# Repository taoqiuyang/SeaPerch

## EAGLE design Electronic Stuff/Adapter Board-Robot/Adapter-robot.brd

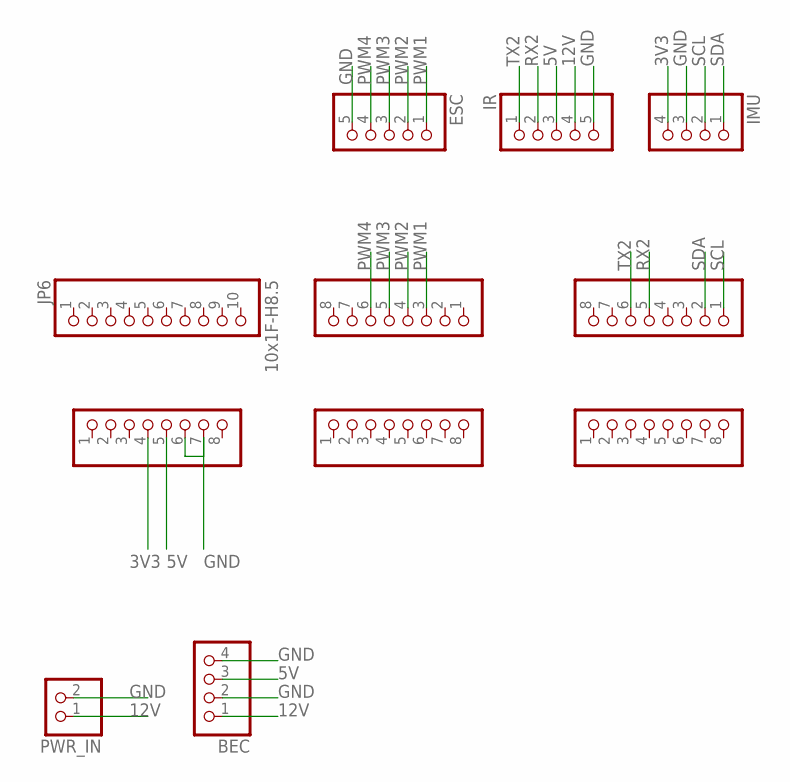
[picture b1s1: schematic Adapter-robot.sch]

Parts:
ADCH: 8x1F-H8.5; 1X08
ADCL: 8x1F-H8.5; 1X08
BEC: PINHD-1X4; 1X04
COMMUNICATION: 8x1F-H8.5; 1X08
ESC: PINHD-1X5; 1X05
IMU: PINHD-1X4; 1X04
IR: PINHD-1X5; 1X05
JP6: 10x1F-H8.5; 1X10
POWER: 8x1F-H8.5; 1X08
PWML: 8x1F-H8.5; 1X08
PWR_IN: PINHD-1X2; 1X02

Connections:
3V3: IMU.4, POWER.4
5V: BEC.3, IR.3, POWER.5
12V: BEC.1, IR.4, PWR_IN.1
GND: BEC.2, BEC.4, ESC.5, IMU.3, IR.5, POWER.6, POWER.7, PWR_IN.2
PWM1: ESC.1, PWML.3
PWM2: ESC.2, PWML.4
PWM3: ESC.3, PWML.5
PWM4: ESC.4, PWML.6
RX2: COMMUNICATION.5, IR.2
SCL: COMMUNICATION.1, IMU.2
SDA: COMMUNICATION.2, IMU.1
TX2: COMMUNICATION.6, IR.1

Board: 2 copper layers, 11 parts (0 on the bottom side), 12 nets, no tracks yet.

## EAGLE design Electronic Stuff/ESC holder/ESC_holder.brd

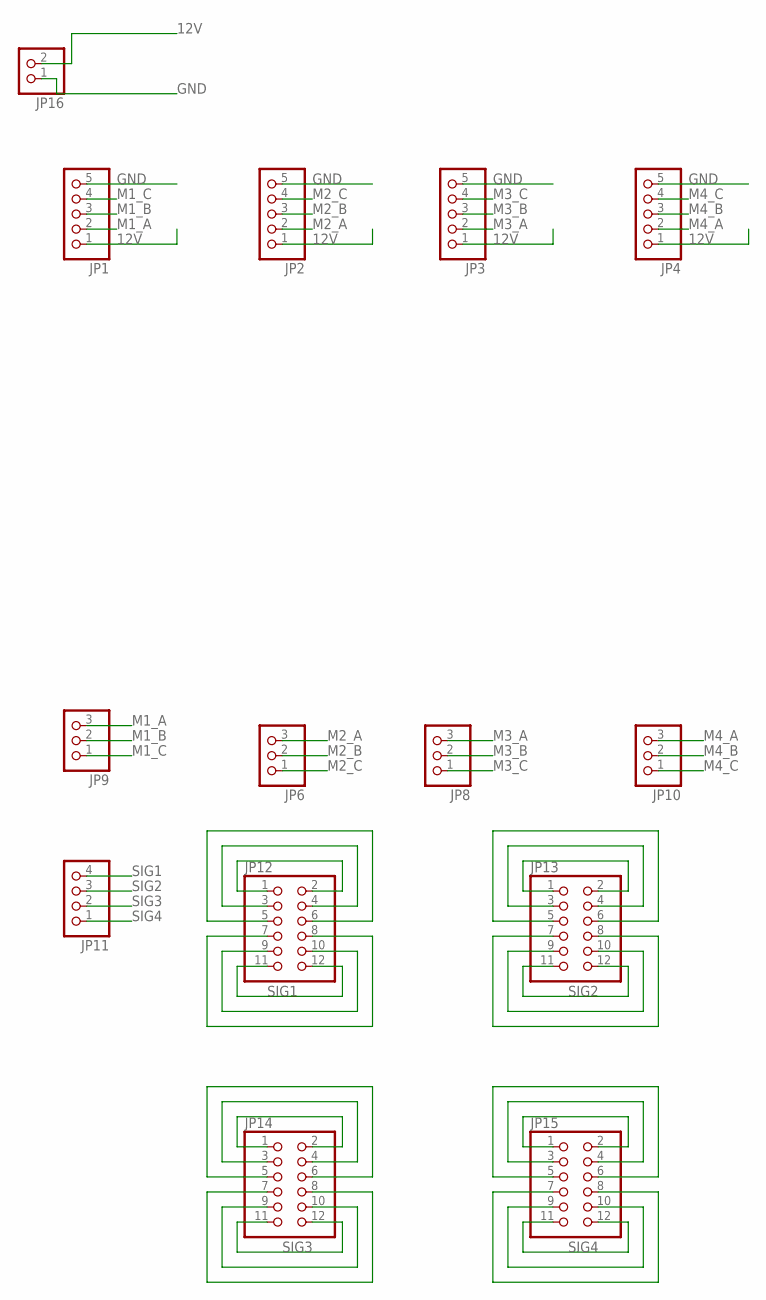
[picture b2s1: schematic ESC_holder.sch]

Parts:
JP1, JP2, JP3, JP4: PINHD-1X5; 1X05
JP6, JP8, JP9, JP10: PINHD-1X3; 1X03
JP11: PINHD-1X4; 1X04
JP12, JP13, JP14, JP15: PINHD-2X6; 2X06
JP16: PINHD-1X2; 1X02

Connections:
12V: JP1.1, JP2.1, JP3.1, JP4.1, JP16.2
GND: JP1.5, JP2.5, JP3.5, JP4.5, JP16.1
M1_A: JP1.2, JP9.3
M1_B: JP1.3, JP9.2
M1_BLACK: JP12.1, JP12.2
M1_BLACK1: JP13.1, JP13.2
M1_BLACK2: JP14.1, JP14.2
M1_BLACK3: JP15.1, JP15.2
M1_C: JP1.4, JP9.1
M2_A: JP2.2, JP6.3
M2_B: JP2.3, JP6.2
M2_C: JP2.4, JP6.1
M3_A: JP3.2, JP8.3
M3_B: JP3.3, JP8.2
M3_C: JP3.4, JP8.1
M4_A: JP4.2, JP10.3
M4_B: JP4.3, JP10.2
M4_C: JP4.4, JP10.1
unnamed: JP13.3, JP13.4
unnamed: JP12.3, JP12.4
unnamed: JP12.5, JP12.6
unnamed: JP12.7, JP12.8
unnamed: JP12.9, JP12.10
unnamed: JP13.5, JP13.6
unnamed: JP13.7, JP13.8
unnamed: JP13.9, JP13.10
unnamed: JP14.3, JP14.4
unnamed: JP14.5, JP14.6
unnamed: JP14.7, JP14.8
unnamed: JP14.9, JP14.10
unnamed: JP15.3, JP15.4
unnamed: JP15.5, JP15.6
unnamed: JP15.7, JP15.8
unnamed: JP15.9, JP15.10
SIG1: JP11.4, JP12.11, JP12.12
SIG2: JP11.3, JP13.11, JP13.12
SIG3: JP11.2, JP14.11, JP14.12
SIG4: JP11.1, JP15.11, JP15.12

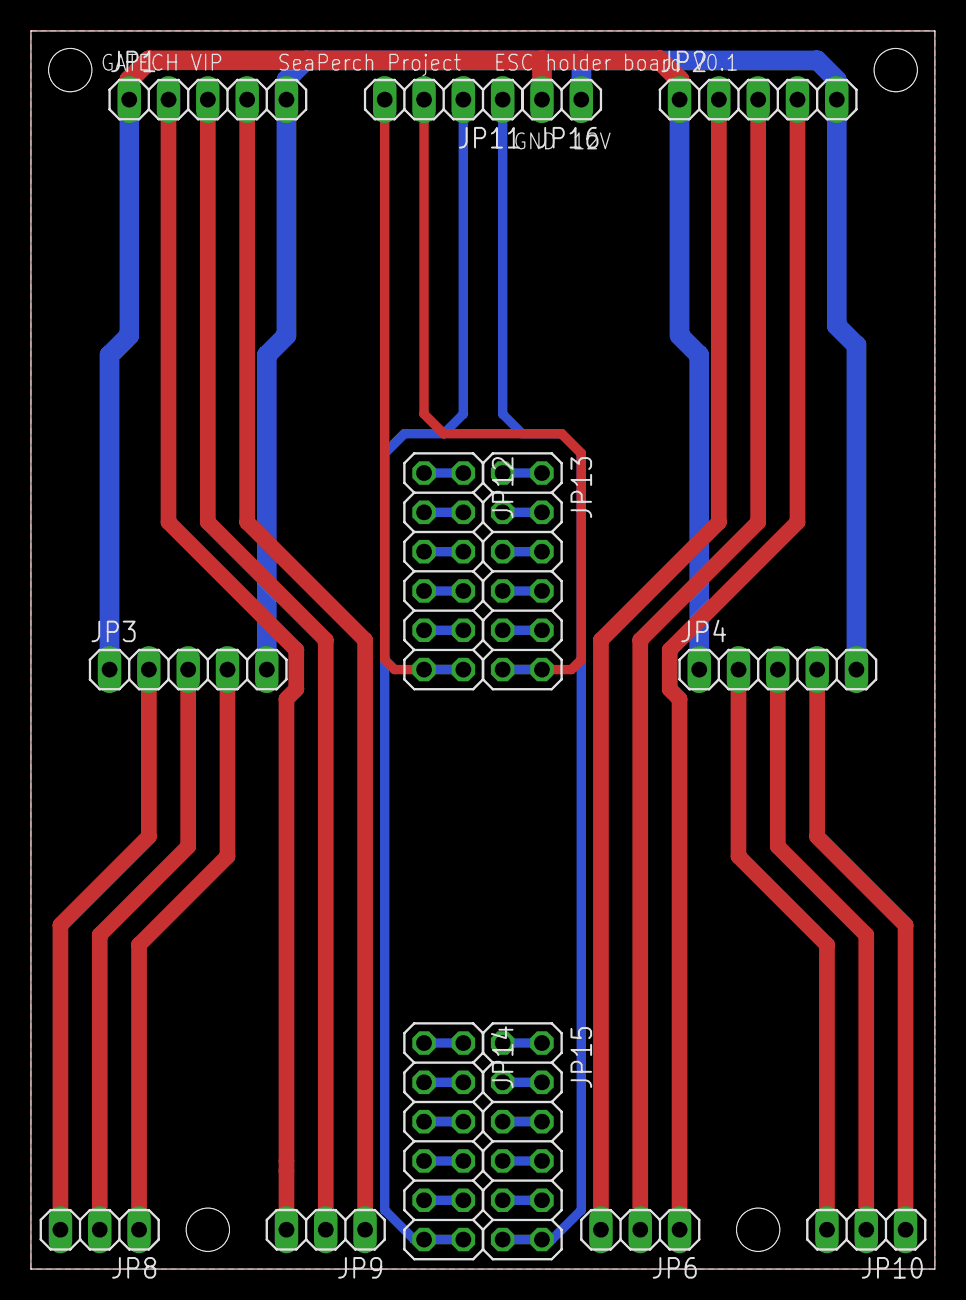
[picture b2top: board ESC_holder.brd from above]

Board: 2 copper layers, 58.4 x 80.0 mm, 14 parts (0 on the bottom side), 38 nets.

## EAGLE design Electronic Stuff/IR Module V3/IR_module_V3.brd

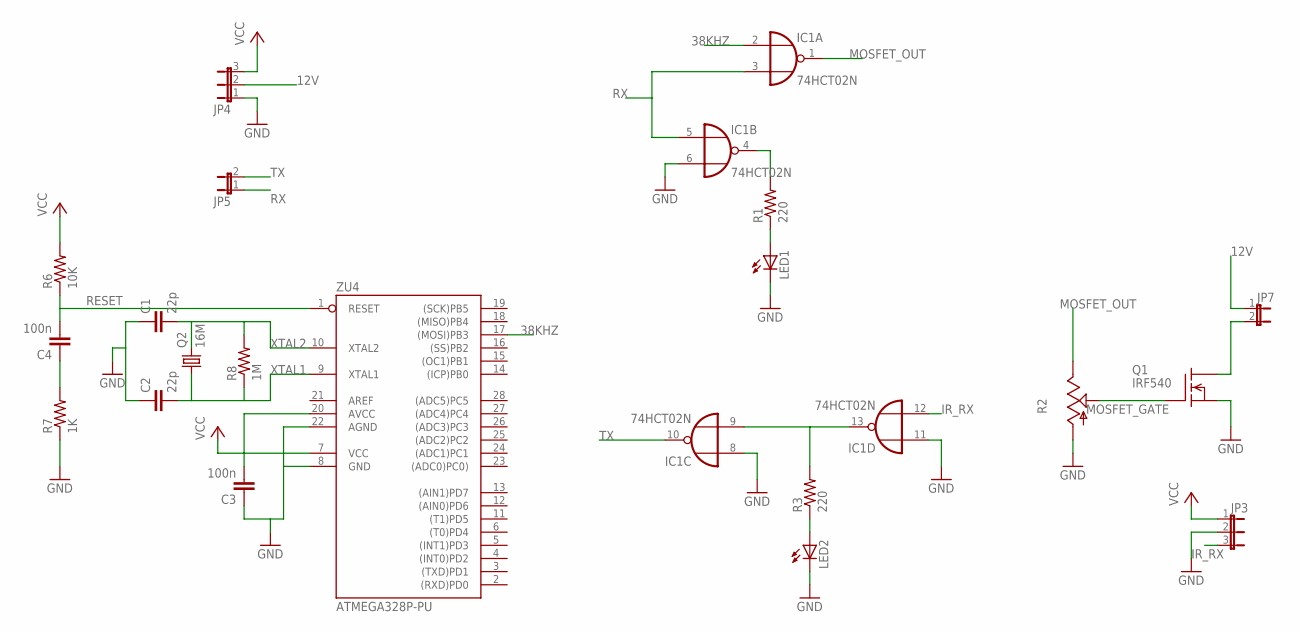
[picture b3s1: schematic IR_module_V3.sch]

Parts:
C1, C2: 22p; CAP-PTH-SMALLEZ
C3, C4: 100n; CAP-PTH-SMALLEZ
IC1: 74HCT02N; DIL14
JP3, JP4: JP2E; JP2
JP5, JP7: JP1E; JP1
LED1, LED2: LED5MM
Q1: IRF540; TO220
Q2: 16M; HC49/S
R1, R3: 220; 0207/10
R2: TRIM_US-B25P; B25P
R6: 10K; 0207/10
R7: 1K; 0207/10
R8: 1M; 0207/10
ZU4: ATMEGA328P-PU; DIL28-3

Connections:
12V: JP4.2, JP7.1
38KHZ: IC1.2 (I0), ZU4.17 ((MOSI)PB3)
GND: C1.1, C2.1, C3.1, IC1.6 (I1), IC1.7 (GND), IC1.8 (I0), IC1.11 (I0), JP3.2, JP4.1, LED1.K (C), LED2.K (C), Q1.3 (S), R2.A, R7.1, ZU4.8 (GND), ZU4.22 (AGND)
IR_RX: IC1.12 (I1), JP3.3
MOSFET_GATE: Q1.1 (G), R2.S
MOSFET_OUT: IC1.1 (O), R2.E
unnamed: IC1.4 (O), R1.2
unnamed: LED1.A, R1.1
unnamed: IC1.9 (I1), IC1.13 (O), R3.2
unnamed: LED2.A, R3.1
unnamed: JP7.2, Q1.2 (D)
unnamed: C4.1, R7.2
RESET: C4.2, R6.1, ZU4.1 (RESET)
RX: IC1.3 (I1), IC1.5 (I0), JP5.1
TX: IC1.10 (O), JP5.2
VCC: C3.2, IC1.14 (VCC), JP3.1, JP4.3, R6.2, ZU4.7 (VCC), ZU4.20 (AVCC)
XTAL1: C2.2, Q2.1, R8.1, ZU4.9 (XTAL1)
XTAL2: C1.2, Q2.2, R8.2, ZU4.10 (XTAL2)

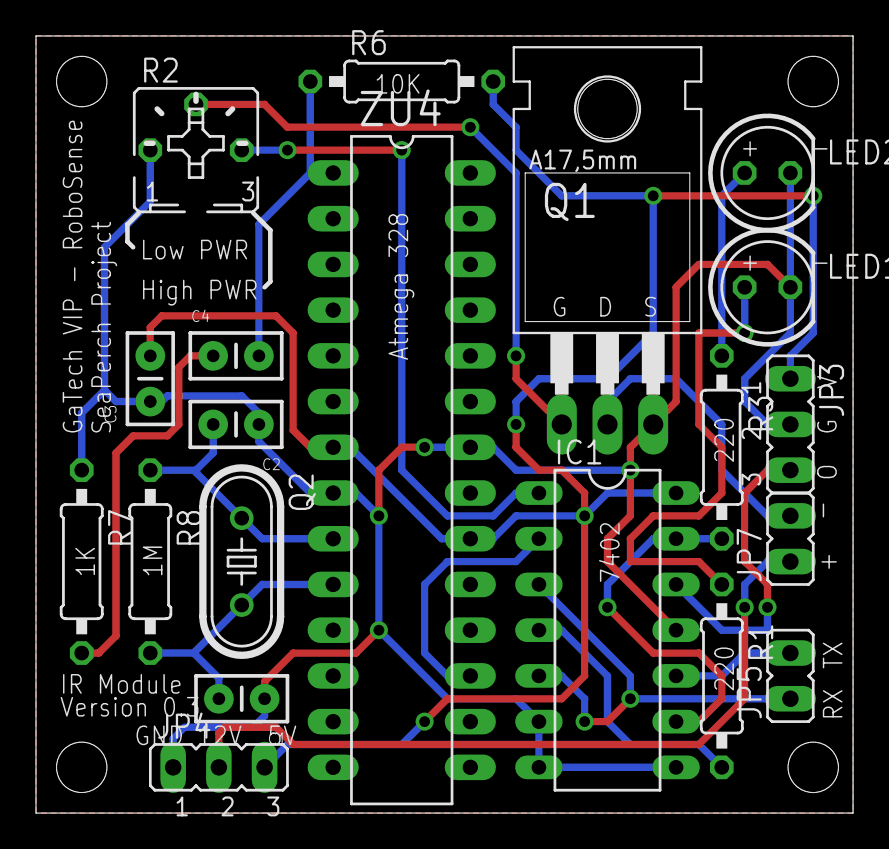
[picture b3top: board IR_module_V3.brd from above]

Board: 2 copper layers, 45.4 x 43.2 mm, 20 parts (0 on the bottom side), 18 nets.

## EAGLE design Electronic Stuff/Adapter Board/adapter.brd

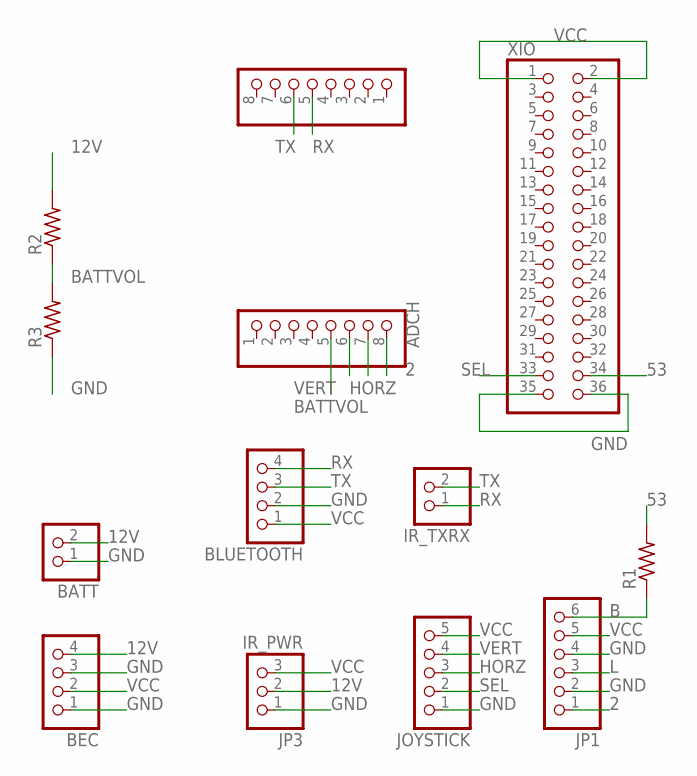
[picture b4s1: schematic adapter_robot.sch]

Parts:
ADCH: 8x1F-H8.5; 1X08
BATT: PINHD-1X2/90; 1X02/90
BEC: PINHD-1X4/90; 1X04/90
BLUETOOTH: PINHD-1X4/90; 1X04/90
COMMUNICATION: 8x1F-H8.5; 1X08
IR_TXRX: PINHD-1X2/90; 1X02/90
JOYSTICK: PINHD-1X5/90; 1X05/90
JP1: PINHD-1X6/90; 1X06/90
JP3: IR_PWR; 1X03/90
R1, R2, R3: R-US_0207/10; 0207/10
XIO: PINHD-2X18; 2X18

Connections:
2: ADCH.8, JP1.1
12V: BATT.2, BEC.4, JP3.2, R2.2
53: R1.2, XIO.34
B: JP1.6, R1.1
BATTVOL: ADCH.5, R2.1, R3.2
GND: BATT.1, BEC.1, BEC.3, BLUETOOTH.2, JOYSTICK.1, JP1.2, JP1.4, JP3.1, R3.1, XIO.35, XIO.36
HORZ: ADCH.7, JOYSTICK.3
L: JP1.3
RX: BLUETOOTH.4, COMMUNICATION.5, IR_TXRX.1
SEL: JOYSTICK.2, XIO.33
TX: BLUETOOTH.3, COMMUNICATION.6, IR_TXRX.2
VCC: BEC.2, BLUETOOTH.1, JOYSTICK.5, JP1.5, JP3.3, XIO.1, XIO.2
VERT: ADCH.6, JOYSTICK.4

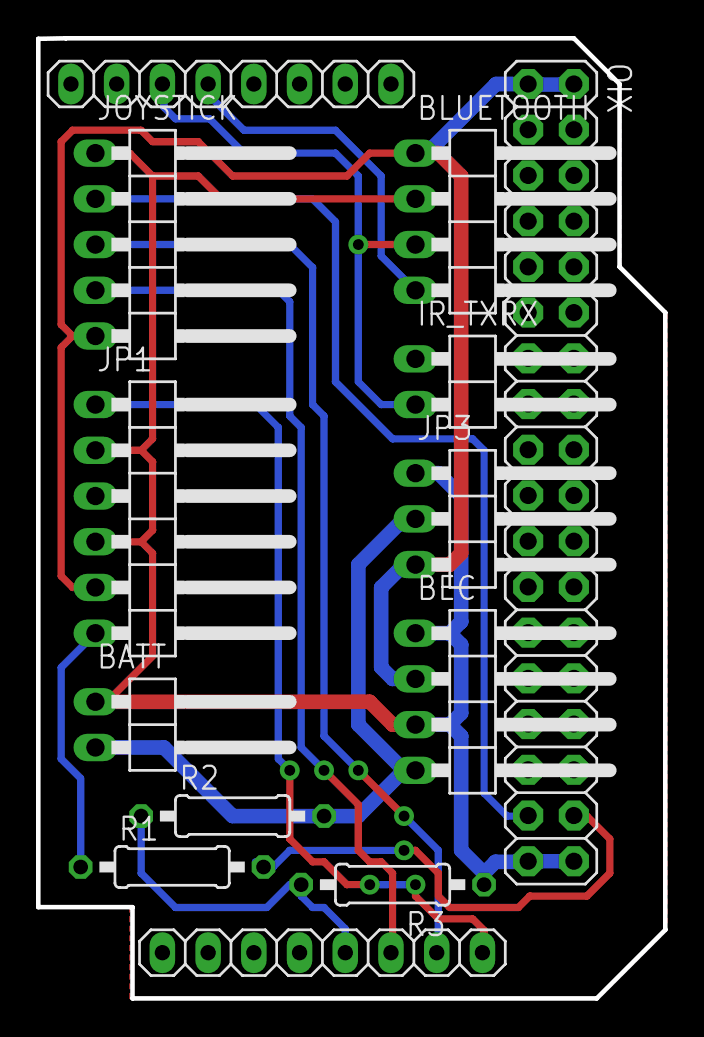
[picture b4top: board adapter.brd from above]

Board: 2 copper layers, 34.8 x 53.3 mm, 13 parts (0 on the bottom side), 12 nets.

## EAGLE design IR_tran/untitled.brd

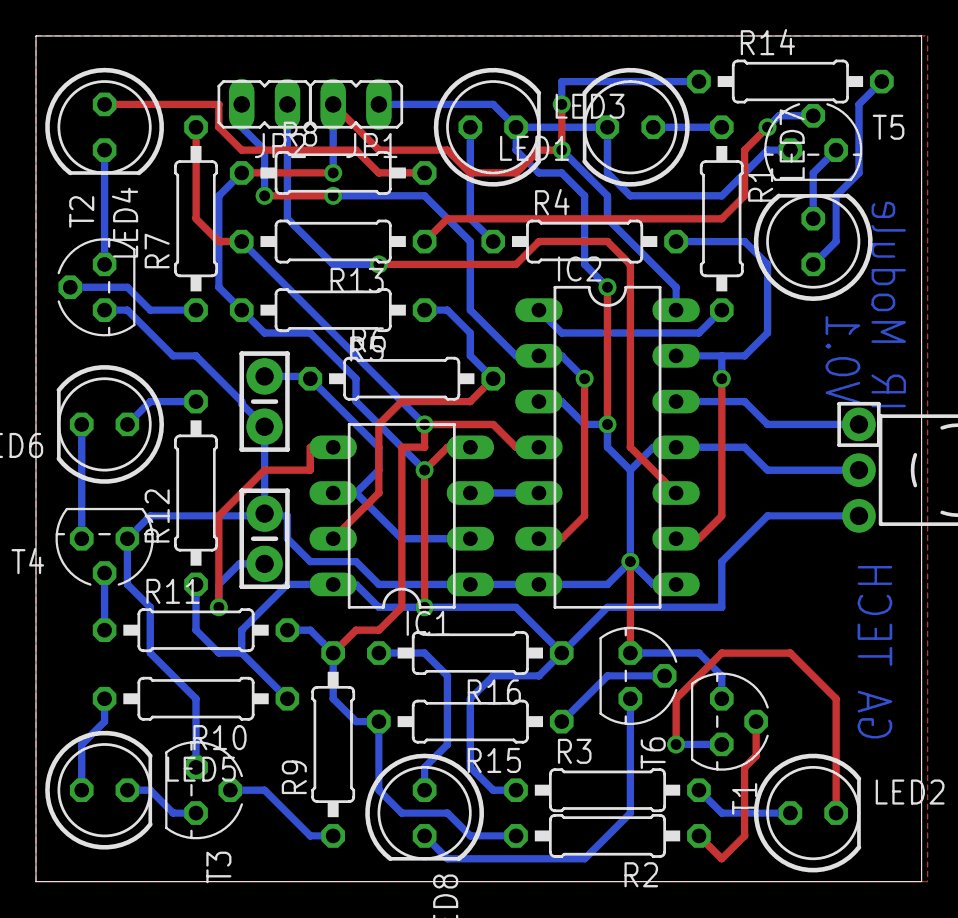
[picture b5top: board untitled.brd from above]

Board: 2 copper layers, 49.2 x 47.0 mm, 37 parts (0 on the bottom side), 32 nets.

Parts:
C1, C2: CAP-PTH-SMALL-KIT
IC1: NE555; DIL-08
IC2: 74HCT02N; DIL14
JP1, JP2: JP1
LED1, LED2, LED3, LED4, LED5, LED6, LED7, LED8: LED5MM
R1, R2, R3, R4, R5, R6, R7, R8, R9, R10, R11, R12, R13, R14, R15, R16: 0207/10
T1, T2, T3, T4, T5, T6: 2N3904; TO92
U1: BRM-2A18VERT; BRM-2508_VERT

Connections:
38KHZ: IC1.3, IC2.5
GND: C1.2, C2.2, IC1.1, IC2.3, IC2.7, IC2.8, IC2.11, JP1.1, LED1.K, LED3.K, T1.3, T2.3, T3.3, T4.3, T5.3, T6.3, U1.2
LED_OUT: IC2.4, R2.2, R7.2, R9.2, R11.2, R13.2, R15.2
unnamed: LED3.A, R4.1
unnamed: LED1.A, R1.1
unnamed: IC2.1, R1.2
unnamed: R2.1, T1.2
unnamed: LED2.A, R3.2
unnamed: LED2.K, T1.1
unnamed: IC2.9, IC2.13, R4.2
unnamed: R7.1, T2.2
unnamed: IC2.12, U1.1
unnamed: LED4.A, R8.2
unnamed: LED4.K, T2.1
unnamed: IC1.7, R5.1, R6.2
unnamed: C1.1, IC1.2, IC1.6, R6.1
unnamed: C2.1, IC1.5
unnamed: R9.1, T3.2
unnamed: LED5.A, R10.2
unnamed: LED5.K, T3.1
unnamed: R11.1, T4.2
unnamed: LED6.A, R12.2
unnamed: LED6.K, T4.1
unnamed: R13.1, T5.2
unnamed: LED7.A, R14.2
unnamed: LED7.K, T5.1
unnamed: R15.1, T6.2
unnamed: LED8.A, R16.2
unnamed: LED8.K, T6.1
RX: IC2.2, IC2.6, JP2.2
TX: IC2.10, JP2.1
VCC: IC1.4, IC1.8, IC2.14, JP1.2, R3.1, R5.2, R8.1, R10.1, R12.1, R14.1, R16.1, U1.3

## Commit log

2015-01-20 Initial source code from Qiuyang Tao
2015-01-20 changed transmission speed of blue tooth from 115200 to 9600
2015-01-20 grouped all joystick related constants into an enum
2015-01-20 removed duplicated code for processJoystick
2015-01-20 code style in processJoystick
2015-01-20 reduced code repetition in serial_2_send_data
2015-01-20 function name format
2015-01-20 added midPoint parameter to processJoystick
2015-01-20 replaced Motor1-5 with an array
2015-01-28 changed serial speed
2015-01-28 added motor count
2015-01-28 removed unused motor initialization
2015-01-28 started moving out motor specs as a separate class
2015-01-28 added header guards, and cpp file
2015-01-28 moved normalized_joystick_Y to MotorSpecs
2015-01-29 added motors array to MotorSpecs class
2015-01-29 migrated motors to MotorSpecs class
2015-01-29 Add LCD display to Controller
2015-01-29 Add Serial Echo Function
2015-01-29 IR transmitter and receiver circuit
2015-02-01 moved joystick button value to MotorSpecs
2015-02-02 Took out text encoding code into TextCoder.h not OO yet
2015-02-02 Took out lcd display code into LCDDisplay.h, not OO yet
2015-02-04 added getMotorCount in MotorSpecs
2015-02-04 Now controlling motor 1&2 instead of 4&5
2015-02-04 Slide_potentiometer_test
2015-02-04 Slide pot implemented (test needed)
2015-02-04 made TextCoder OO
2015-02-05 used temporary object instead of pointer for TextCoder
2015-02-05 renamed TextCoder to ControlSideTextCoder for clarity
2015-02-06 added ControlSideCoder interface
2015-02-06 deleted legacy forward declaration
2015-02-06 replaced MotorSpecs pointer with object
2015-02-06 added a copy constructor for MotorSpecs class
2015-02-06 moved library inclusion from child class to parent abstract class
2015-02-11 Bluetooth transmission in byte stream (rough implementation, lots of polishing needed)
2015-02-11 byteUtils
2015-02-13 CAD file for water seal
2015-02-13 Low power IR driver simulation
2015-02-13 Low Power IR module PCB file
2015-02-14 Dimensions of
2015-02-14 LowIR
2015-02-14 Serial and slide pot test
2015-02-14 Several Test Photos
2015-02-14 Libraries for IMU and Motor driver
2015-02-14 Add IMU
2015-02-14 Depth Sensor Library
2015-02-14 Add Depth Sensor
2015-02-14 commented out sensor code that could be problematic
2015-02-14 slide pot working!
2015-02-14 removed debugging print statements
2015-02-14 adjusted code format
2015-02-14 commented out initSensors
2015-02-14 changed motor shield board address
2015-02-14 sensor data now available
2015-02-14 Add PID example (NOT for depth keeping)
2015-02-14 moved code shared by both controller and robot to library
2015-02-14 moved third-party libraries into vendor folder
2015-02-14 added SeaPerch library
2015-02-15 added vendor libraries
2015-02-15 deleted PID related code for compilation
2015-02-15 Depth Sensor and IMU Data Output
2015-02-15 PID_test
2015-02-15 added SeaPerch prefix to library files
2015-02-15 rename
2015-02-15 added RobotSideCoder abstract base class
2015-02-15 pulled out MotorExecutor code (not OO yet)
2015-02-15 Add PID
2015-02-15 Map motor3 values for PID
2015-02-15 PID libs
2015-02-15 sensor output format
2015-02-15 got rid of obsolete data transmission
2015-02-15 renamed variables in MotorExecutor
2015-02-15 simplying MotorExecutor code
2015-02-15 added necessary libraries to MotorExecutor
2015-02-15 started converting MotorExecutor to OO
2015-02-15 dimensions for arduino and shields from Hanjie
2015-02-15 Renamed constants in MotorExecutor
2015-02-15 moved implementation to MotorExecutor.cpp
2015-02-16 controller box
2015-02-16 renamed integer variable in BinaryUtils code
2015-02-17 Add Draft water proof solution
2015-02-19 Tube Design
2015-02-21 Tube for electronics
2015-02-21 IR module V0.2
2015-02-21 IR module V0.2 with Manufacturing GERBER files
2015-02-21 Some photos about IR V0.2
2015-02-21 PCB of IR module V0.1
2015-02-21 Draft 3D plots for water proof solution
2015-02-25 Add New Pin Definitions
2015-02-25 control pin enum
2015-02-25 control pin enum member rename
2015-02-25 fixed typo in processJoystick
2015-02-25 implemented calibrate
2015-02-25 took out enum into header file
2015-02-25 ControlReader class
2015-02-25 ControlReader cpp
2015-02-25 move reading slide pot into control reader
2015-02-25 const correctness for ControlReader class
2015-02-25 processJoystick double division
2015-02-25 processJoystick algorithm simplification
2015-02-25 renamed MotorSpecs to ControlSpecs
2015-02-25 use ControlReader to fill ControlSpecs
2015-02-25 improved style of ControlSpecs
2015-02-25 const correctness for ControlSpecs
2015-02-25 now ControlReader just fill a ControlSpecs
2015-02-25 eliminated unused variable in processJoystick
2015-02-25 processJoystick now return float
2015-02-25 const correctness for BinaryUtils
2015-02-25 BinaryUtils int to char array without using mask
2015-02-25 made BinaryUtils OO
2015-02-25 custom bytecpy like memcpy
2015-02-25 BinaryUtils now supports float to byte array conversion and vice versa
2015-02-25 fixed a typo
2015-02-25 simplified ControlSideByteCoder code
2015-02-25 moved delay out of byte coder
2015-02-25 able to transmit normalized joystick data and slide pot data
2015-02-26 ByteCoder buffer size
2015-02-26 execute motors using joystick values instead of motor values
2015-02-26 Some dimensions for parts
2015-02-26 Some test photos
2015-02-26 set motor still when joystick value is zero
2015-02-26 logic in processJoystick
2015-02-26 made motor less sensitive
2015-02-26 corrected motor direction
2015-02-26 made motor even less sensitive
2015-02-26 took out executeJoystickCommand function
2015-02-26 slide pot motor control
2015-02-26 coder no longer send motor values
2015-02-26 deleted deprecated TextCoder
2015-02-26 corrected an error that slidePot was sent as float instead of int
2015-02-26 removed motor related statements from controller and robot
2015-02-26 removed all motor value related statements
2015-03-02 took out constants in MotorExecutor code
2015-03-02 moved PID into MotorExecutor
2015-03-02 execute in MotorExecutor now takes current depth in addition to control specs
2015-03-02 renamed MotorExecutor functions for generalization
2015-03-02 renamed several variables in MotorExecutor
2015-03-03 Aluminium Structure CAD files
    Also compatible with plastic if proper thickness is used
2015-03-03 Test code for new BLDC motor
    The motor ESC cannot recognize signal for Servo.write(x) function if
    x<20
2015-03-03 Adapter board design files with GERBER
2015-03-03 Draft tube design
2015-03-03 MotorExecutor initialize with baseline pressure
2015-03-03 const correctness for MotorExecutor functions
2015-03-03 added depth control mode for vertical motor
2015-03-04 moved source code under src folder
2015-03-11 plot log and test photos
2015-03-11 just for fun :)
2015-03-15 IR Module V3
2015-03-15 Revert "IR Module V3"
    This reverts commit 299ccce0db33e314ff60d4235ae697a04a211f65.
2015-03-15 Revert "Revert "IR Module V3""
    This reverts commit 0c102e2696405be111570d6e1ddb8861bae37577.
2015-03-15 Fixed several minor issues
2015-03-15 Adjusted pin directions
2015-03-15 New PCB layout
2015-03-15 IR module V3 complete manufacture files
2015-03-15 IR module V4
    New Layout，supports multi-turn potentiometer
2015-03-15 Changed TX-RX pin locations
2015-03-15 Added some texts
2015-03-15 Manufacture GERBER files processed for IR module V4
2015-03-15 Added texts
2015-03-15 Minor Adjustment for Manufacturing
2015-03-15 bkup file
2015-03-17 test photos
2015-03-17 test video
2015-03-18 ESC holder board with GERBER files
2015-03-18 IR module PCB sent to manifacturer
2015-03-18 ESC holder PCB sent to manifacturer
2015-03-18 robot side adapter board
2015-03-21 Change baud rate of IR
2015-03-21 resolved a library importation error from using Arduino 1.6.1
2015-03-21 decreased controlSpecs to serial delay to increase responsiveness
2015-03-21 added slide pot control mode to controlSpecs
2015-03-21 renamed variable in controlSpecs
2015-03-21 BLDC test
2015-03-21 reduced code repetition in ControlSideByteCoder
2015-03-21 const correctness for ControlSideByteCoder
2015-03-21 renamed a variable
2015-03-21 made a generic lcd display function
2015-03-22 improved lcdDisplay argument convenience (now accepting a single string delimited by '\n' )
2015-03-22 print welcome screen with new LCD display method
2015-03-22 simplified getKey logic
2015-03-25 Assembled structures
2015-04-04 updated BLDC test
2015-04-04 ESC setting Table
2015-04-06 horizontal motors done
2015-04-06 switched to new motors
2015-04-07 fixed missing returns and algorithm bugs in AlgoUtils
2015-04-07 removed debug print
2015-04-12 algo utils forgot to commit
2015-04-12 revert: shouldn't use constexpr
2015-04-12 sync problem
2015-04-12 made lcdDisplayer oo
2015-04-12 made KeyDetector OO
2015-04-12 added keypad id to ControlPin
2015-04-12 key detector returns key detected
2015-04-12 renamed getKey to mapKey
2015-04-12 slide pot mode selection done
2015-04-12 prevent other function from using controlMode by making it static in function
2015-04-12 static in function oldKey
2015-04-12 last commit did not remove oldKey cleanly
2015-04-12 lcd display default speed control message
2015-04-12 code cleaning and enhancement
2015-04-12 completed ControlPin
2015-04-13 renamed ControlMode to DepthControlMode
2015-04-13 renamed DepthControlMode enum elements
2015-04-13 slidePotMode to depthControlMode
2015-04-13 added speed control mode
2015-04-13 SpeedControlMode implemented
2015-04-13 updated control pin
2015-04-13 code clean up for RC_Robot
2015-04-13 read battery voltage
2015-04-13 RC_Robot code clean up
2015-04-13 code clean up
2015-04-14 read robot orientation
2015-04-14 RobotData toSerial skeleton
2015-04-14 robot orientation class
2015-04-14 created SerialUitls library
2015-04-14 send robot data
2015-04-14 made fromSerial block until data available
2015-04-14 data to controlled done
2015-04-14 differentiated controller and robot message by using different message headers
2015-04-14 clear read buffer garbage
2015-04-14 clear own read buffer immediate after write
2015-04-15 current state of work. Motor control fine, robot data error rate too high
2015-04-30 made IR bidirectional communication work
2015-05-07 some dimensions
2015-05-07 Draft solution of Ambient light sensor
2015-05-09 Robot-side adapter board
2015-05-11 Robot-side adapter board, ZIP file
2015-05-11 Revert "Robot-side adapter board"
    This reverts commit 0ccd179ffe9678df28f2aac372d4ea96e5d87f4b.
2015-05-11 Revert "Revert "Robot-side adapter board""
    This reverts commit fb628dfa1f0818bea8d9edb3eb4b62aba7686d09.
2015-05-14 PID lib and Adapter board
2015-08-14 Rubber ring
2015-09-06 added rotational selectable menu
2015-09-06 fixed a bug of missing reference of robot data in LCDDisplayer
2015-09-06 fixed a bug of up scrolling index out of bound
2015-09-15 Emergency brake robot motors in case of no signal
2015-09-16 refactored motor control functions in MotorExecutor
2015-11-13 added serial/can adapter
2015-11-13 use interrupt instead

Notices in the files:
parts and their libraries:
SparkFun-Capacitors: Licensing: Creative Commons ShareAlike 4.0 International - https://creativecommons.org/licenses/by-sa/4.0
